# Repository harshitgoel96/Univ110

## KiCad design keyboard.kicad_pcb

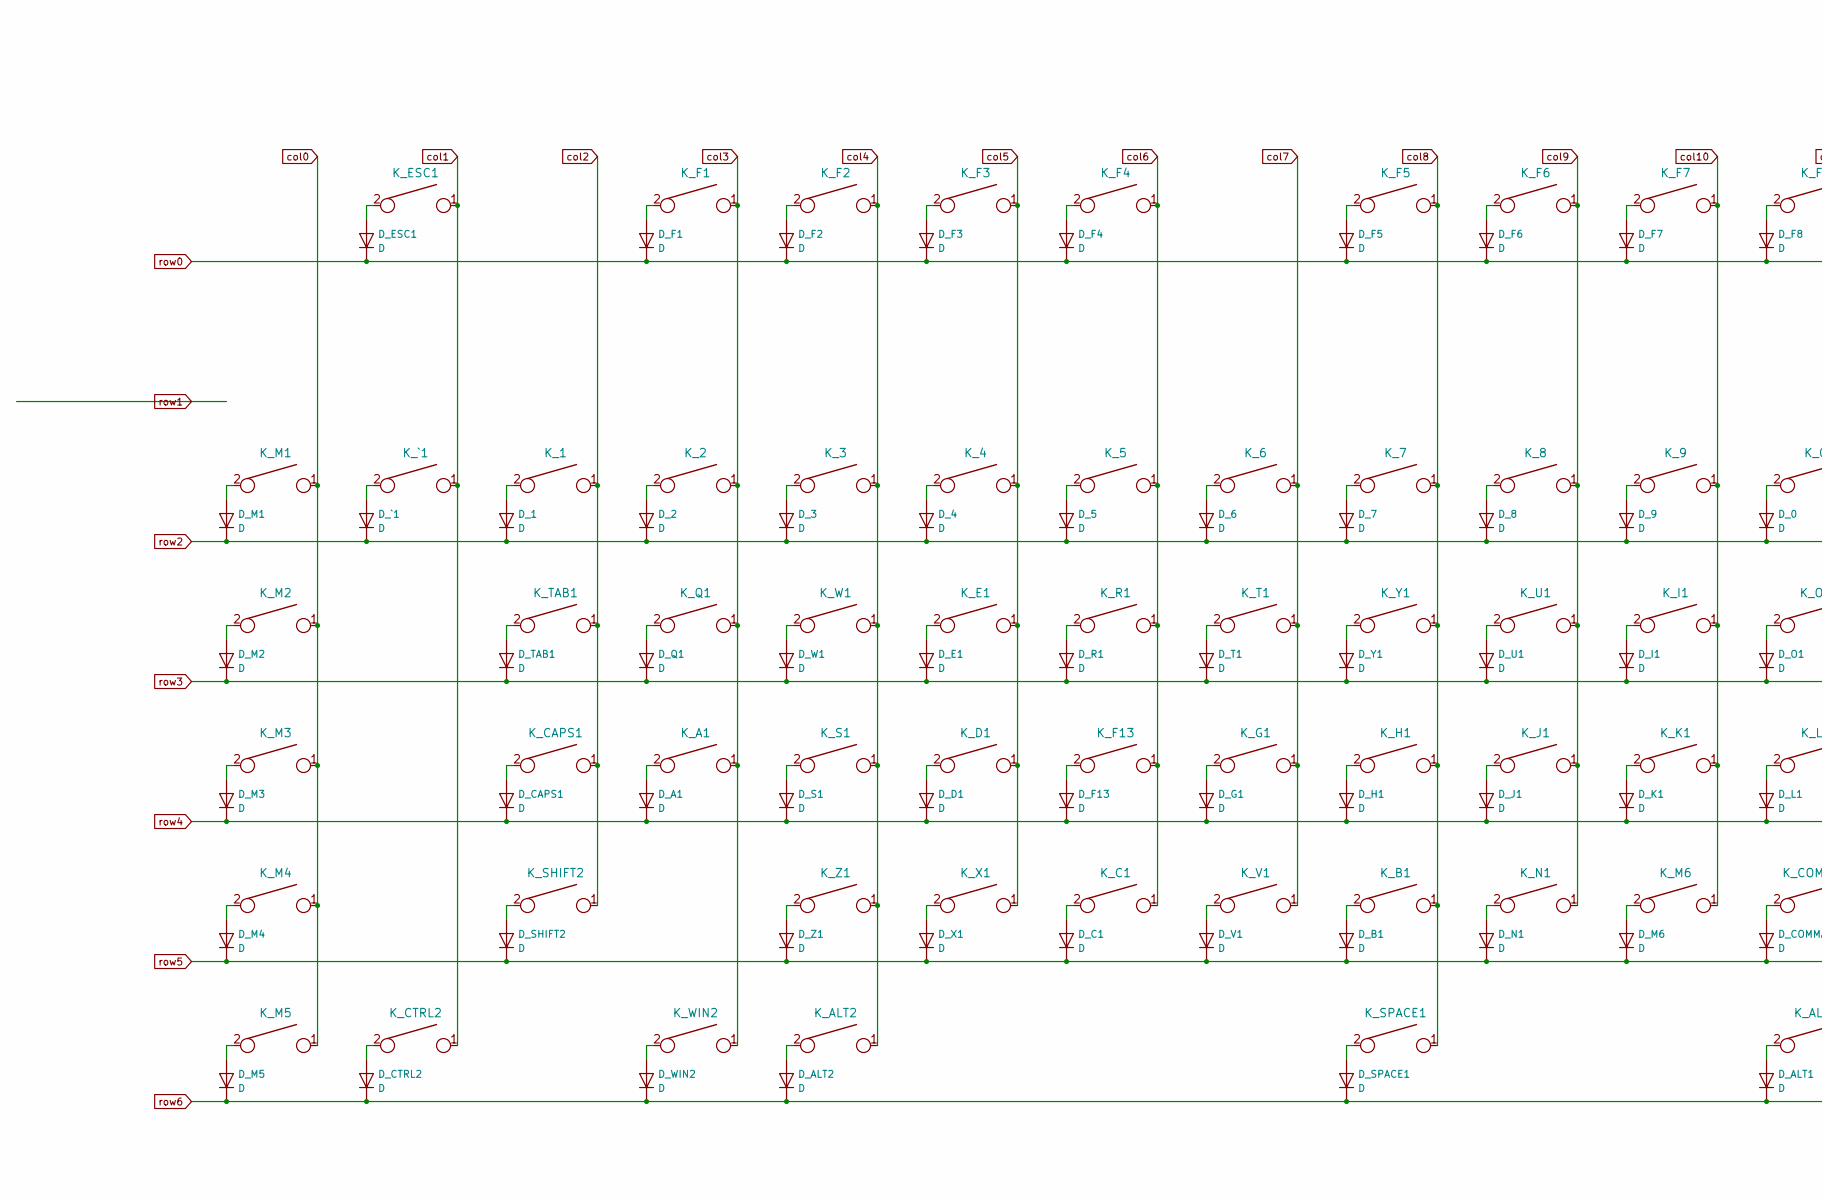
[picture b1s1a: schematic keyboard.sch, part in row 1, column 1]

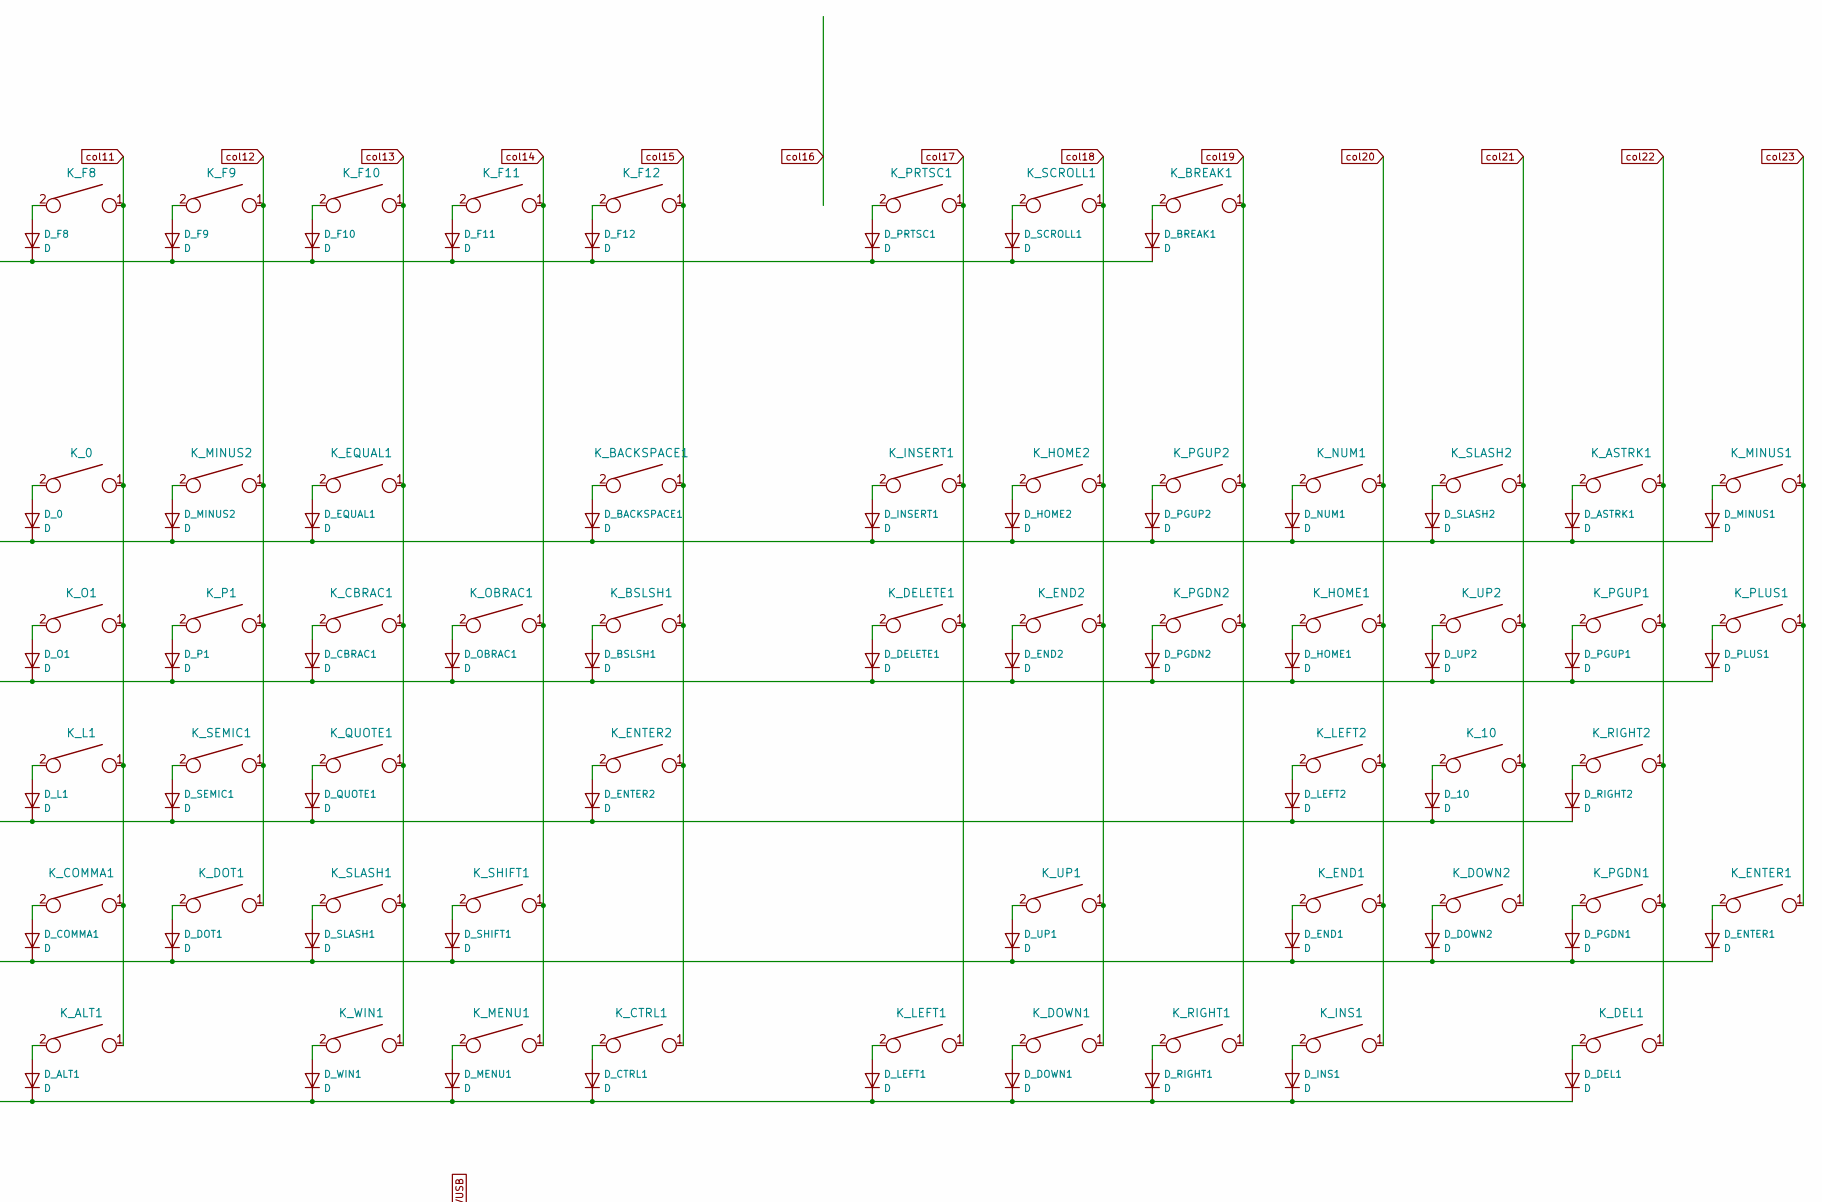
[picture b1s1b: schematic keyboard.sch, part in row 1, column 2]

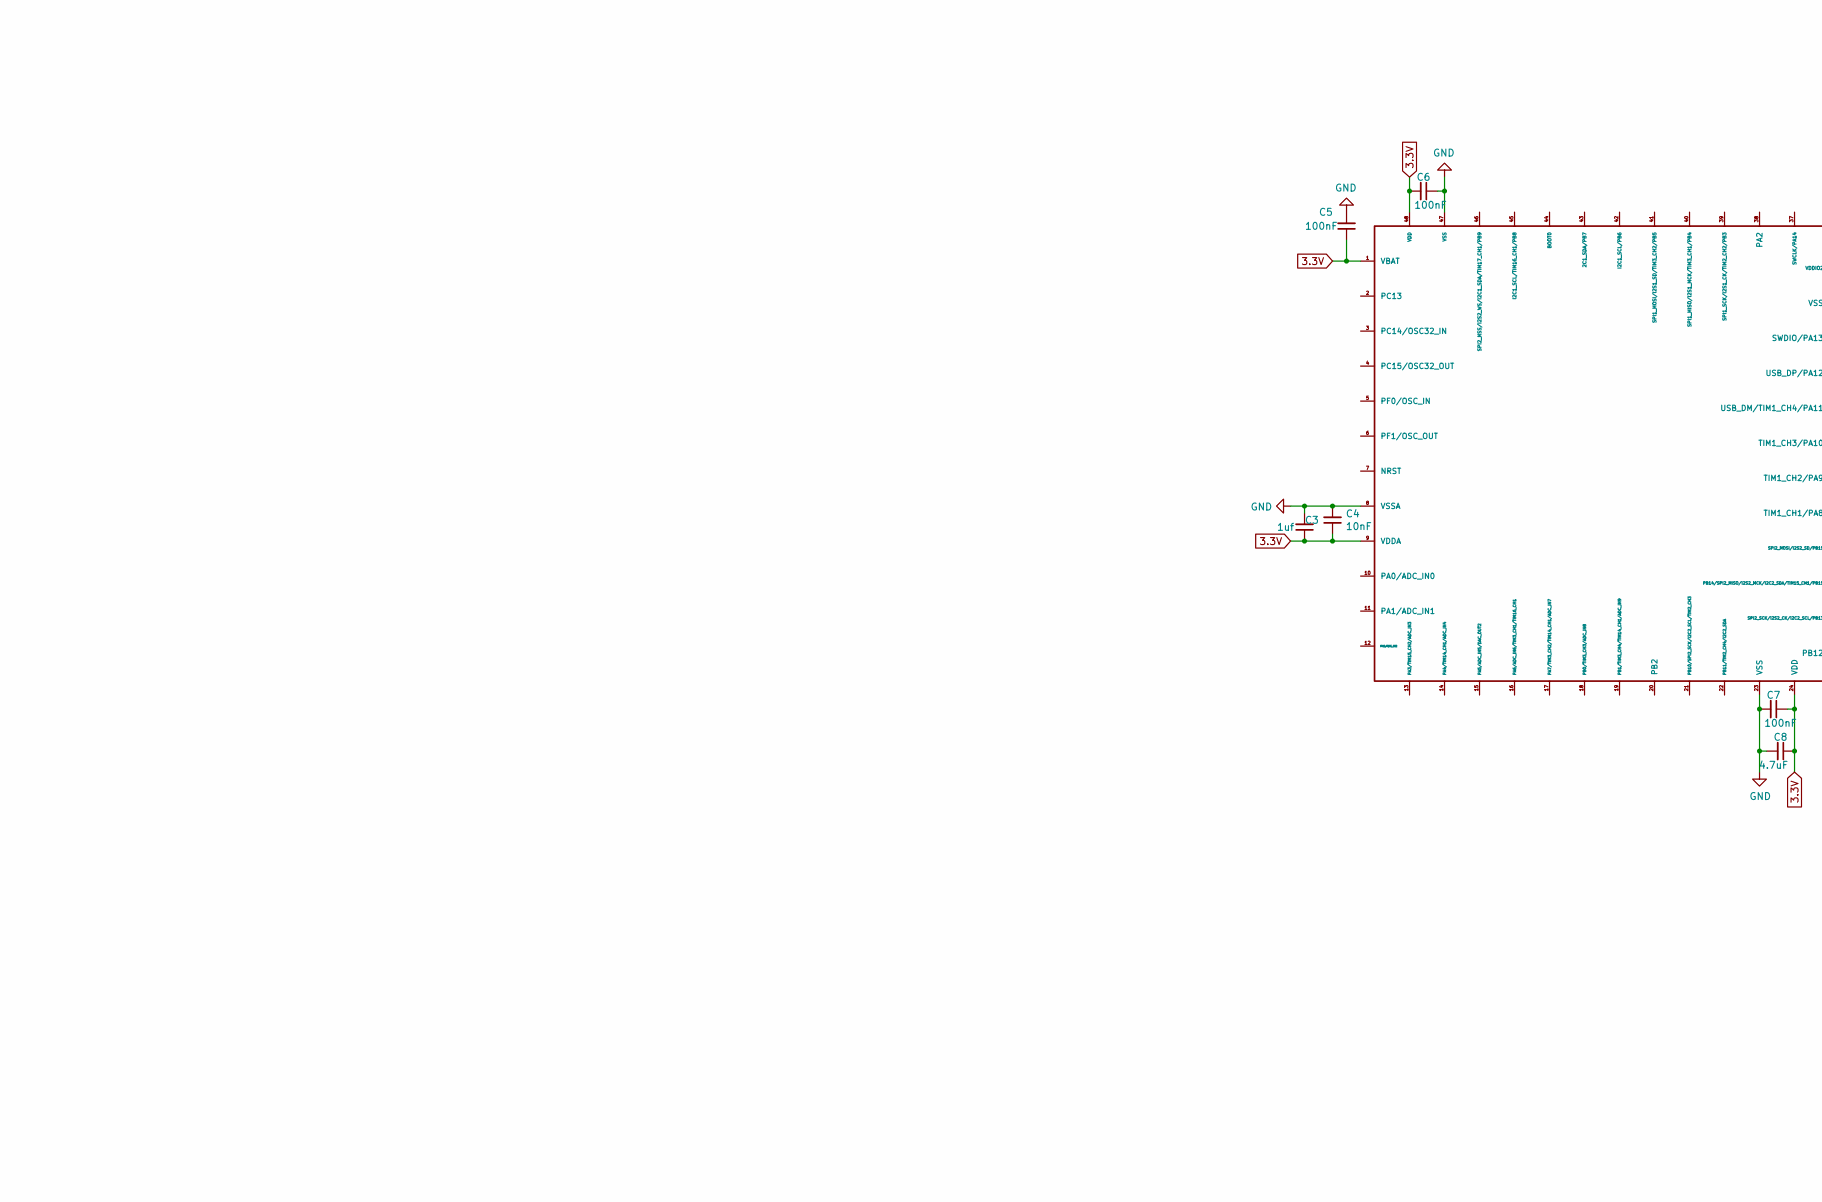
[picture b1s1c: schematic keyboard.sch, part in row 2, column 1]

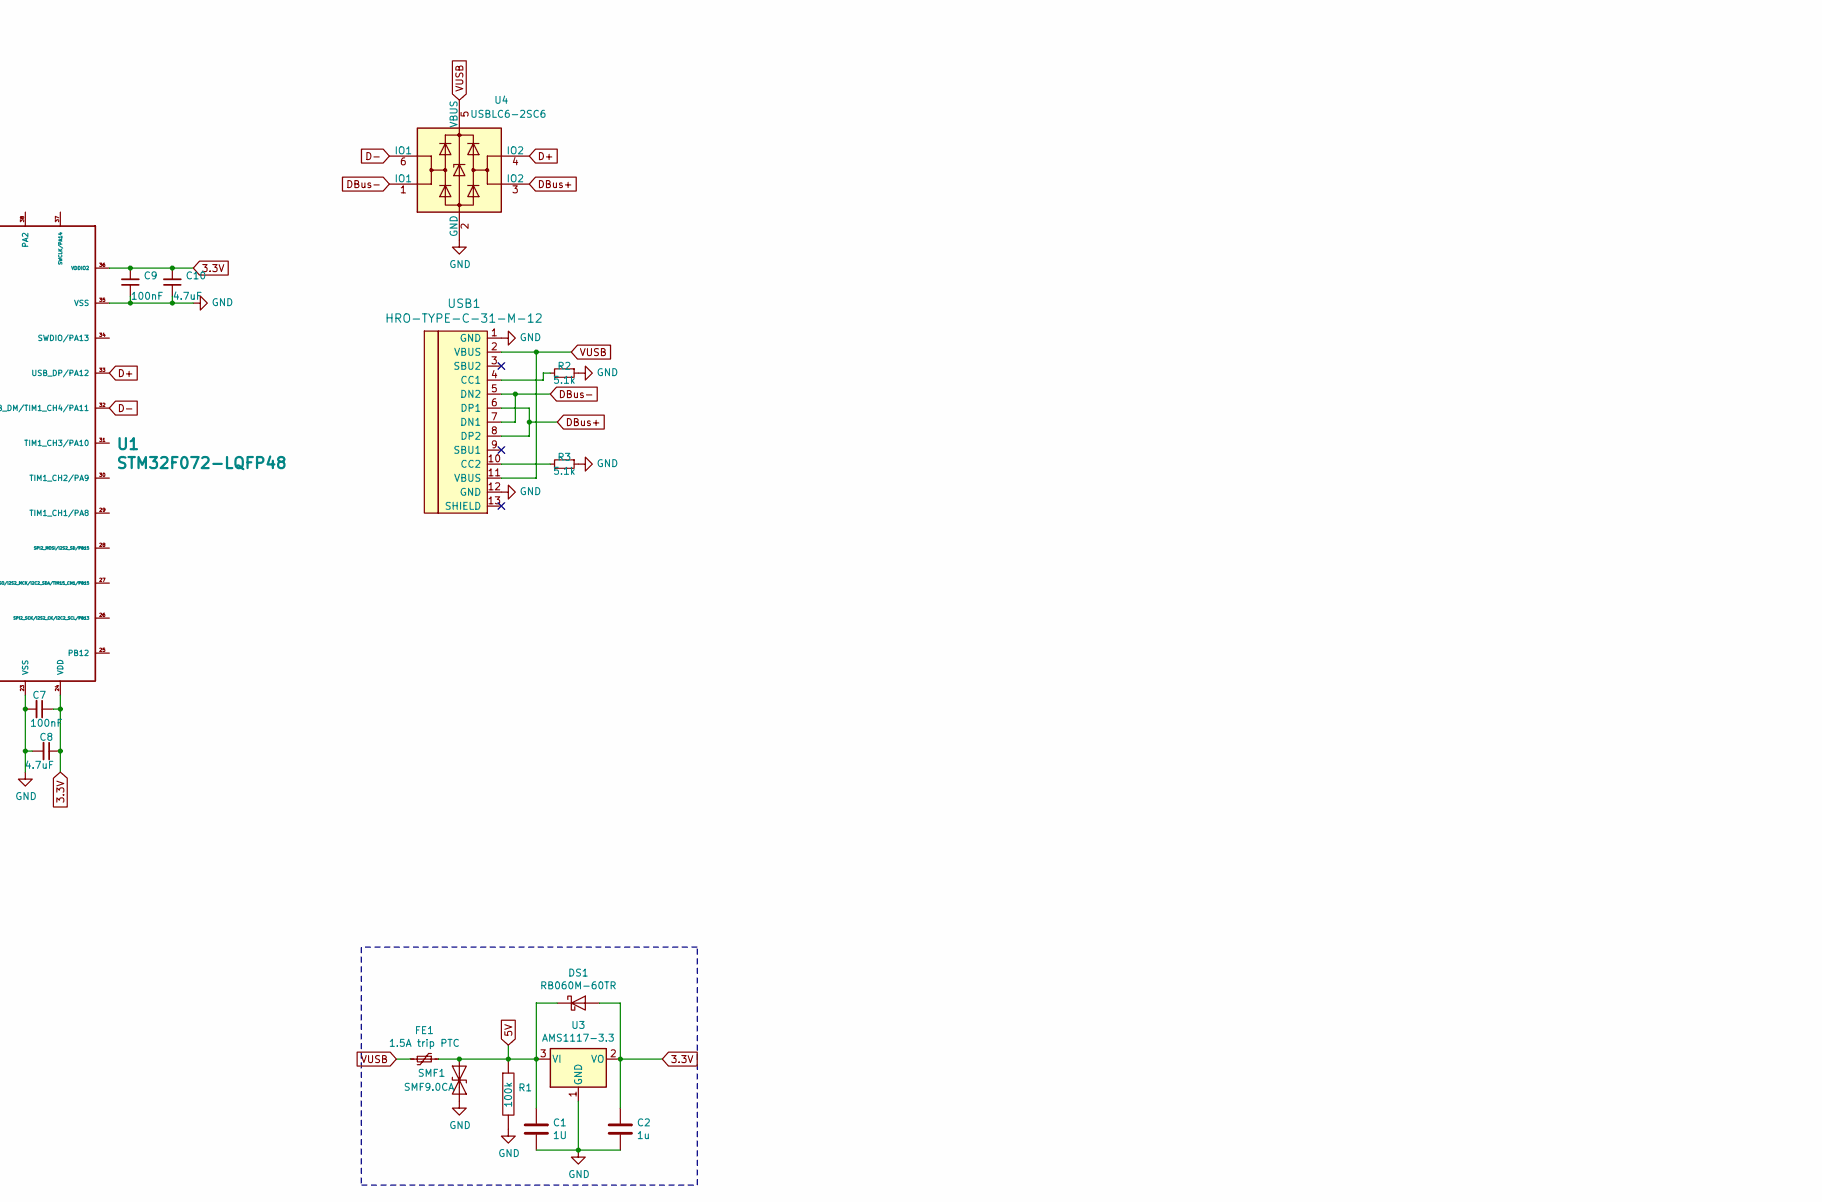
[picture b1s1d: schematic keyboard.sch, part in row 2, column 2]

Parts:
C1: 1U; C_0805_2012Metric_Pad1.15x1.40mm_HandSolder
C2: 1u; C_0805_2012Metric_Pad1.15x1.40mm_HandSolder
C3: 1uf; C_0805_2012Metric_Pad1.15x1.40mm_HandSolder
C4: 10nF; C_0805_2012Metric_Pad1.15x1.40mm_HandSolder
C5, C6, C7, C9: 100nF; C_0805_2012Metric_Pad1.15x1.40mm_HandSolder
C8, C10: 4.7uF; C_0805_2012Metric_Pad1.15x1.40mm_HandSolder
DS1: RB060M-60TR; D_SOD-123
D_0, D_1, D_2, D_3, D_4, D_5, D_6, D_7, D_8, D_9, D_10: D; D_SOD123_axial
D_A1: D; D_SOD123_axial
D_ALT1, D_ALT2: D; D_SOD123_axial
D_ASTRK1: D; D_SOD123_axial
D_B1: D; D_SOD123_axial
D_BACKSPACE1: D; D_SOD123_axial
D_BREAK1: D; D_SOD123_axial
D_BSLSH1: D; D_SOD123_axial
D_C1: D; D_SOD123_axial
D_CAPS1: D; D_SOD123_axial
D_CBRAC1: D; D_SOD123_axial
D_COMMA1: D; D_SOD123_axial
D_CTRL1, D_CTRL2: D; D_SOD123_axial
D_D1: D; D_SOD123_axial
D_DEL1: D; D_SOD123_axial
D_DELETE1: D; D_SOD123_axial
D_DOT1: D; D_SOD123_axial
D_DOWN1, D_DOWN2: D; D_SOD123_axial
D_E1: D; D_SOD123_axial
D_END1, D_END2: D; D_SOD123_axial
D_ENTER1, D_ENTER2: D; D_SOD123_axial
D_EQUAL1: D; D_SOD123_axial
D_ESC1: D; D_SOD123_axial
D_F1, D_F2, D_F3, D_F4, D_F5, D_F6, D_F7, D_F8, D_F9, D_F10, D_F11, D_F12, D_F13: D; D_SOD123_axial
D_G1: D; D_SOD123_axial
D_H1: D; D_SOD123_axial
D_HOME1, D_HOME2: D; D_SOD123_axial
D_I1: D; D_SOD123_axial
D_INS1: D; D_SOD123_axial
D_INSERT1: D; D_SOD123_axial
D_J1: D; D_SOD123_axial
D_K1: D; D_SOD123_axial
D_L1: D; D_SOD123_axial
D_LEFT1, D_LEFT2: D; D_SOD123_axial
D_M1, D_M2, D_M3, D_M4, D_M5, D_M6: D; D_SOD123_axial
D_MENU1: D; D_SOD123_axial
D_MINUS1, D_MINUS2: D; D_SOD123_axial
D_N1: D; D_SOD123_axial
D_NUM1: D; D_SOD123_axial
D_O1: D; D_SOD123_axial
D_OBRAC1: D; D_SOD123_axial
D_P1: D; D_SOD123_axial
D_PGDN1, D_PGDN2: D; D_SOD123_axial
D_PGUP1, D_PGUP2: D; D_SOD123_axial
D_PLUS1: D; D_SOD123_axial
D_PRTSC1: D; D_SOD123_axial
D_Q1: D; D_SOD123_axial
D_QUOTE1: D; D_SOD123_axial
D_R1: D; D_SOD123_axial
D_RIGHT1, D_RIGHT2: D; D_SOD123_axial
D_S1: D; D_SOD123_axial
D_SCROLL1: D; D_SOD123_axial
D_SEMIC1: D; D_SOD123_axial
D_SHIFT1, D_SHIFT2: D; D_SOD123_axial
D_SLASH1, D_SLASH2: D; D_SOD123_axial
D_SPACE1: D; D_SOD123_axial
D_T1: D; D_SOD123_axial
D_TAB1: D; D_SOD123_axial
D_U1: D; D_SOD123_axial
D_UP1, D_UP2: D; D_SOD123_axial
D_V1: D; D_SOD123_axial
D_W1: D; D_SOD123_axial
D_WIN1, D_WIN2: D; D_SOD123_axial
D_X1: D; D_SOD123_axial
D_Y1: D; D_SOD123_axial
D_Z1: D; D_SOD123_axial
D_`1: D; D_SOD123_axial
FE1: 1.5A trip PTC; Fuse_1812_4532
K_0, K_1, K_2, K_3, K_4, K_5, K_6, K_7, K_8, K_9, K_10: KEYSW; MX-ALPs-PG1350-FLIP
K_A1: KEYSW; MX-ALPs-PG1350-FLIP
K_ALT1, K_ALT2: KEYSW; MX-ALPs-PG1350-FLIP
K_ASTRK1: KEYSW; MX-ALPs-PG1350-FLIP
K_B1: KEYSW; MX-ALPs-PG1350-FLIP
K_BACKSPACE1: KEYSW; MX-ALPs-PG1350-FLIP-2U-FLIP
K_BREAK1: KEYSW; MX-ALPs-PG1350-FLIP
K_BSLSH1: KEYSW; MX-ALPs-PG1350-FLIP
K_C1: KEYSW; MX-ALPs-PG1350-FLIP
K_CAPS1: KEYSW; MX-ALPs-PG1350-FLIP
K_CBRAC1: KEYSW; MX-ALPs-PG1350-FLIP
K_COMMA1: KEYSW; MX-ALPs-PG1350-FLIP
K_CTRL1, K_CTRL2: KEYSW; MX-ALPs-PG1350-FLIP
K_D1: KEYSW; MX-ALPs-PG1350-FLIP
K_DEL1: KEYSW; MX-ALPs-PG1350-FLIP
K_DELETE1: KEYSW; MX-ALPs-PG1350-FLIP
K_DOT1: KEYSW; MX-ALPs-PG1350-FLIP
K_DOWN1, K_DOWN2: KEYSW; MX-ALPs-PG1350-FLIP
K_E1: KEYSW; MX-ALPs-PG1350-FLIP
K_END1, K_END2: KEYSW; MX-ALPs-PG1350-FLIP
K_ENTER1: KEYSW; MX-ALPs-PG1350-FLIP-2U
K_ENTER2: KEYSW; MX-ALPs-PG1350-FLIP-2U-FLIP
K_EQUAL1: KEYSW; MX-ALPs-PG1350-FLIP
K_ESC1: KEYSW; MX-ALPs-PG1350-FLIP
K_F1, K_F2, K_F3, K_F4, K_F5, K_F6, K_F7, K_F8, K_F9, K_F10, K_F11, K_F12, K_F13: KEYSW; MX-ALPs-PG1350-FLIP
K_G1: KEYSW; MX-ALPs-PG1350-FLIP
K_H1: KEYSW; MX-ALPs-PG1350-FLIP
K_HOME1, K_HOME2: KEYSW; MX-ALPs-PG1350-FLIP
K_I1: KEYSW; MX-ALPs-PG1350-FLIP
K_INS1: KEYSW; MX-ALPs-PG1350-FLIP-2U
K_INSERT1: KEYSW; MX-ALPs-PG1350-FLIP
K_J1: KEYSW; MX-ALPs-PG1350-FLIP
K_K1: KEYSW; MX-ALPs-PG1350-FLIP
K_L1: KEYSW; MX-ALPs-PG1350-FLIP
K_LEFT1, K_LEFT2: KEYSW; MX-ALPs-PG1350-FLIP
K_M1, K_M2, K_M3, K_M4, K_M5, K_M6: KEYSW; MX-ALPs-PG1350-FLIP
K_MENU1: KEYSW; MX-ALPs-PG1350-FLIP
K_MINUS1, K_MINUS2: KEYSW; MX-ALPs-PG1350-FLIP
K_N1: KEYSW; MX-ALPs-PG1350-FLIP
K_NUM1: KEYSW; MX-ALPs-PG1350-FLIP
K_O1: KEYSW; MX-ALPs-PG1350-FLIP
K_OBRAC1: KEYSW; MX-ALPs-PG1350-FLIP
K_P1: KEYSW; MX-ALPs-PG1350-FLIP
K_PGDN1, K_PGDN2: KEYSW; MX-ALPs-PG1350-FLIP
K_PGUP1, K_PGUP2: KEYSW; MX-ALPs-PG1350-FLIP
K_PLUS1: KEYSW; MX-ALPs-PG1350-FLIP-2U
K_PRTSC1: KEYSW; MX-ALPs-PG1350-FLIP
K_Q1: KEYSW; MX-ALPs-PG1350-FLIP
K_QUOTE1: KEYSW; MX-ALPs-PG1350-FLIP
K_R1: KEYSW; MX-ALPs-PG1350-FLIP
K_RIGHT1, K_RIGHT2: KEYSW; MX-ALPs-PG1350-FLIP
K_S1: KEYSW; MX-ALPs-PG1350-FLIP
K_SCROLL1: KEYSW; MX-ALPs-PG1350-FLIP
K_SEMIC1: KEYSW; MX-ALPs-PG1350-FLIP
K_SHIFT1, K_SHIFT2: KEYSW; MX-ALPs-PG1350-FLIP-2U-FLIP
K_SLASH1, K_SLASH2: KEYSW; MX-ALPs-PG1350-FLIP
K_SPACE1: KEYSW; MX625_base
K_T1: KEYSW; MX-ALPs-PG1350-FLIP
K_TAB1: KEYSW; MX-ALPs-PG1350-FLIP
K_U1: KEYSW; MX-ALPs-PG1350-FLIP
K_UP1, K_UP2: KEYSW; MX-ALPs-PG1350-FLIP
K_V1: KEYSW; MX-ALPs-PG1350-FLIP
K_W1: KEYSW; MX-ALPs-PG1350-FLIP
K_WIN1, K_WIN2: KEYSW; MX-ALPs-PG1350-FLIP
K_X1: KEYSW; MX-ALPs-PG1350-FLIP
K_Y1: KEYSW; MX-ALPs-PG1350-FLIP
K_Z1: KEYSW; MX-ALPs-PG1350-FLIP
K_`1: KEYSW; MX-ALPs-PG1350-FLIP
R1: 100k; R_0805
R2, R3: 5.1k; R_0805
SMF1: SMF9.0CA; D_SOD-123
U1: STM32F072-LQFP48; LQFP-48_7x7mm_P0.5mm
U3: AMS1117-3.3; SOT-223-3_TabPin2
U4: USBLC6-2SC6; SOT-23-6
USB1: HRO-TYPE-C-31-M-12; HRO-TYPE-C-31-M-12-HandSoldering

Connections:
3.3V: C2.1, C3.1, C4.1, C5.1, C6.2, C7.1, C8.1, C9.2, C10.2, DS1.2 (A), U1.1 (VBAT), U1.9 (VDDA), U1.24 (VDD), U1.36 (VDDIO2), U1.48 (VDD), U3.2 (VO)
5V: C1.1, DS1.1 (K), FE1.1, R1.1, SMF1.1 (A1), U3.3 (VI)
D+: U1.33 (USB_DP/PA12), U4.4 (IO2)
D-: U1.32 (USB_DM/TIM1_CH4/PA11), U4.6 (IO1)
DBus+: U4.3 (IO2), USB1.6 (DP1), USB1.8 (DP2)
DBus-: U4.1 (IO1), USB1.5 (DN2), USB1.7 (DN1)
GND: C1.2, C2.2, C3.2, C4.2, C5.2, C6.1, C7.2, C8.2, C9.1, C10.1, R1.2, R2.1, R3.1, SMF1.2 (A2), U1.8 (VSSA), U1.23 (VSS), U1.35 (VSS), U1.47 (VSS), U3.1 (GND), U4.2 (GND), USB1.1 (GND), USB1.12 (GND)
unnamed: D_0.2 (A), K_0.2
unnamed: D_1.2 (A), K_1.2
unnamed: D_2.2 (A), K_2.2
unnamed: D_3.2 (A), K_3.2
unnamed: D_4.2 (A), K_4.2
unnamed: D_5.2 (A), K_5.2
unnamed: D_6.2 (A), K_6.2
unnamed: D_7.2 (A), K_7.2
unnamed: D_8.2 (A), K_8.2
unnamed: D_9.2 (A), K_9.2
unnamed: D_10.2 (A), K_10.2
unnamed: D_A1.2 (A), K_A1.2
unnamed: D_ALT1.2 (A), K_ALT1.2
unnamed: D_ALT2.2 (A), K_ALT2.2
unnamed: D_ASTRK1.2 (A), K_ASTRK1.2
unnamed: D_B1.2 (A), K_B1.2
unnamed: D_BACKSPACE1.2 (A), K_BACKSPACE1.2
unnamed: D_BREAK1.2 (A), K_BREAK1.2
unnamed: D_BSLSH1.2 (A), K_BSLSH1.2
unnamed: D_C1.2 (A), K_C1.2
unnamed: D_CAPS1.2 (A), K_CAPS1.2
unnamed: D_CBRAC1.2 (A), K_CBRAC1.2
unnamed: D_COMMA1.2 (A), K_COMMA1.2
unnamed: D_CTRL1.2 (A), K_CTRL1.2
unnamed: D_CTRL2.2 (A), K_CTRL2.2
unnamed: D_D1.2 (A), K_D1.2
unnamed: D_DEL1.2 (A), K_DEL1.2
unnamed: D_DELETE1.2 (A), K_DELETE1.2
unnamed: D_DOT1.2 (A), K_DOT1.2
unnamed: D_DOWN1.2 (A), K_DOWN1.2
unnamed: D_DOWN2.2 (A), K_DOWN2.2
unnamed: D_E1.2 (A), K_E1.2
unnamed: D_END1.2 (A), K_END1.2
unnamed: D_END2.2 (A), K_END2.2
unnamed: D_ENTER1.2 (A), K_ENTER1.2
unnamed: D_ENTER2.2 (A), K_ENTER2.2
unnamed: D_EQUAL1.2 (A), K_EQUAL1.2
unnamed: D_ESC1.2 (A), K_ESC1.2
unnamed: D_F1.2 (A), K_F1.2
unnamed: D_F2.2 (A), K_F2.2
unnamed: D_F3.2 (A), K_F3.2
unnamed: D_F4.2 (A), K_F4.2
unnamed: D_F5.2 (A), K_F5.2
unnamed: D_F6.2 (A), K_F6.2
unnamed: D_F7.2 (A), K_F7.2
unnamed: D_F8.2 (A), K_F8.2
unnamed: D_F9.2 (A), K_F9.2
unnamed: D_F10.2 (A), K_F10.2
unnamed: D_F11.2 (A), K_F11.2
unnamed: D_F12.2 (A), K_F12.2
unnamed: D_F13.2 (A), K_F13.2
unnamed: D_G1.2 (A), K_G1.2
unnamed: D_H1.2 (A), K_H1.2
unnamed: D_HOME1.2 (A), K_HOME1.2
unnamed: D_HOME2.2 (A), K_HOME2.2
unnamed: D_I1.2 (A), K_I1.2
unnamed: D_INS1.2 (A), K_INS1.2
unnamed: D_INSERT1.2 (A), K_INSERT1.2
unnamed: D_J1.2 (A), K_J1.2
unnamed: D_K1.2 (A), K_K1.2
unnamed: D_L1.2 (A), K_L1.2
unnamed: D_LEFT1.2 (A), K_LEFT1.2
unnamed: D_LEFT2.2 (A), K_LEFT2.2
unnamed: D_M1.2 (A), K_M1.2
unnamed: D_M2.2 (A), K_M2.2
unnamed: D_M3.2 (A), K_M3.2
unnamed: D_M4.2 (A), K_M4.2
unnamed: D_M5.2 (A), K_M5.2
unnamed: D_M6.2 (A), K_M6.2
unnamed: D_MENU1.2 (A), K_MENU1.2
unnamed: D_MINUS1.2 (A), K_MINUS1.2
unnamed: D_MINUS2.2 (A), K_MINUS2.2
unnamed: D_N1.2 (A), K_N1.2
unnamed: D_NUM1.2 (A), K_NUM1.2
unnamed: D_O1.2 (A), K_O1.2
unnamed: D_OBRAC1.2 (A), K_OBRAC1.2
unnamed: D_P1.2 (A), K_P1.2
unnamed: D_PGDN1.2 (A), K_PGDN1.2
unnamed: D_PGDN2.2 (A), K_PGDN2.2
unnamed: D_PGUP1.2 (A), K_PGUP1.2
unnamed: D_PGUP2.2 (A), K_PGUP2.2
unnamed: D_PLUS1.2 (A), K_PLUS1.2
unnamed: D_PRTSC1.2 (A), K_PRTSC1.2
unnamed: D_Q1.2 (A), K_Q1.2
unnamed: D_QUOTE1.2 (A), K_QUOTE1.2
unnamed: D_R1.2 (A), K_R1.2
unnamed: D_RIGHT1.2 (A), K_RIGHT1.2
unnamed: D_RIGHT2.2 (A), K_RIGHT2.2
unnamed: D_S1.2 (A), K_S1.2
unnamed: D_SCROLL1.2 (A), K_SCROLL1.2
unnamed: D_SEMIC1.2 (A), K_SEMIC1.2
unnamed: D_SHIFT1.2 (A), K_SHIFT1.2
unnamed: D_SHIFT2.2 (A), K_SHIFT2.2
unnamed: D_SLASH1.2 (A), K_SLASH1.2
unnamed: D_SLASH2.2 (A), K_SLASH2.2
unnamed: D_SPACE1.2 (A), K_SPACE1.2
unnamed: D_T1.2 (A), K_T1.2
unnamed: D_TAB1.2 (A), K_TAB1.2
unnamed: D_U1.2 (A), K_U1.2
unnamed: D_UP1.2 (A), K_UP1.2
unnamed: D_UP2.2 (A), K_UP2.2
unnamed: D_V1.2 (A), K_V1.2
unnamed: D_W1.2 (A), K_W1.2
unnamed: D_WIN1.2 (A), K_WIN1.2
unnamed: D_WIN2.2 (A), K_WIN2.2
unnamed: D_X1.2 (A), K_X1.2
unnamed: D_Y1.2 (A), K_Y1.2
unnamed: D_Z1.2 (A), K_Z1.2
unnamed: D_`1.2 (A), K_`1.2
unnamed: R2.2, USB1.4 (CC1)
unnamed: R3.2, USB1.10 (CC2)
VUSB: FE1.2, U4.5 (VBUS), USB1.2 (VBUS), USB1.11 (VBUS)
col0: K_M1.1, K_M2.1, K_M3.1, K_M4.1, K_M5.1
col1: K_CTRL2.1, K_ESC1.1, K_`1.1
col2: K_1.1, K_CAPS1.1, K_SHIFT2.1, K_TAB1.1
col3: K_2.1, K_A1.1, K_F1.1, K_Q1.1, K_WIN2.1
col4: K_3.1, K_ALT2.1, K_F2.1, K_S1.1, K_W1.1, K_Z1.1
col5: K_4.1, K_D1.1, K_E1.1, K_F3.1, K_X1.1
col6: K_5.1, K_C1.1, K_F4.1, K_F13.1, K_R1.1
col7: K_6.1, K_G1.1, K_T1.1, K_V1.1
col8: K_7.1, K_B1.1, K_F5.1, K_H1.1, K_SPACE1.1, K_Y1.1
col9: K_8.1, K_F6.1, K_J1.1, K_N1.1, K_U1.1
col10: K_9.1, K_F7.1, K_I1.1, K_K1.1, K_M6.1
col11: K_0.1, K_ALT1.1, K_COMMA1.1, K_F8.1, K_L1.1, K_O1.1
col12: K_DOT1.1, K_F9.1, K_MINUS2.1, K_P1.1, K_SEMIC1.1
col13: K_CBRAC1.1, K_EQUAL1.1, K_F10.1, K_QUOTE1.1, K_SLASH1.1, K_WIN1.1
col14: K_F11.1, K_MENU1.1, K_OBRAC1.1, K_SHIFT1.1
col15: K_BACKSPACE1.1, K_BSLSH1.1, K_CTRL1.1, K_ENTER2.1, K_F12.1
col17: K_DELETE1.1, K_INSERT1.1, K_LEFT1.1, K_PRTSC1.1
col18: K_DOWN1.1, K_END2.1, K_HOME2.1, K_SCROLL1.1, K_UP1.1
col19: K_BREAK1.1, K_PGDN2.1, K_PGUP2.1, K_RIGHT1.1
col20: K_END1.1, K_HOME1.1, K_INS1.1, K_LEFT2.1, K_NUM1.1
col21: K_10.1, K_DOWN2.1, K_SLASH2.1, K_UP2.1
col22: K_ASTRK1.1, K_DEL1.1, K_PGDN1.1, K_PGUP1.1, K_RIGHT2.1
col23: K_ENTER1.1, K_MINUS1.1, K_PLUS1.1
row0: D_BREAK1.1 (K), D_ESC1.1 (K), D_F1.1 (K), D_F2.1 (K), D_F3.1 (K), D_F4.1 (K), D_F5.1 (K), D_F6.1 (K), D_F7.1 (K), D_F8.1 (K), D_F9.1 (K), D_F10.1 (K), D_F11.1 (K), D_F12.1 (K), D_PRTSC1.1 (K), D_SCROLL1.1 (K)
row2: D_0.1 (K), D_1.1 (K), D_2.1 (K), D_3.1 (K), D_4.1 (K), D_5.1 (K), D_6.1 (K), D_7.1 (K), D_8.1 (K), D_9.1 (K), D_ASTRK1.1 (K), D_BACKSPACE1.1 (K), D_EQUAL1.1 (K), D_HOME2.1 (K), D_INSERT1.1 (K), D_M1.1 (K), D_MINUS1.1 (K), D_MINUS2.1 (K), D_NUM1.1 (K), D_PGUP2.1 (K), D_SLASH2.1 (K), D_`1.1 (K)
row3: D_BSLSH1.1 (K), D_CBRAC1.1 (K), D_DELETE1.1 (K), D_E1.1 (K), D_END2.1 (K), D_HOME1.1 (K), D_I1.1 (K), D_M2.1 (K), D_O1.1 (K), D_OBRAC1.1 (K), D_P1.1 (K), D_PGDN2.1 (K), D_PGUP1.1 (K), D_PLUS1.1 (K), D_Q1.1 (K), D_R1.1 (K), D_T1.1 (K), D_TAB1.1 (K), D_U1.1 (K), D_UP2.1 (K), D_W1.1 (K), D_Y1.1 (K)
row4: D_10.1 (K), D_A1.1 (K), D_CAPS1.1 (K), D_D1.1 (K), D_ENTER2.1 (K), D_F13.1 (K), D_G1.1 (K), D_H1.1 (K), D_J1.1 (K), D_K1.1 (K), D_L1.1 (K), D_LEFT2.1 (K), D_M3.1 (K), D_QUOTE1.1 (K), D_RIGHT2.1 (K), D_S1.1 (K), D_SEMIC1.1 (K)
row5: D_B1.1 (K), D_C1.1 (K), D_COMMA1.1 (K), D_DOT1.1 (K), D_DOWN2.1 (K), D_END1.1 (K), D_ENTER1.1 (K), D_M4.1 (K), D_M6.1 (K), D_N1.1 (K), D_PGDN1.1 (K), D_SHIFT1.1 (K), D_SHIFT2.1 (K), D_SLASH1.1 (K), D_UP1.1 (K), D_V1.1 (K), D_X1.1 (K), D_Z1.1 (K)
row6: D_ALT1.1 (K), D_ALT2.1 (K), D_CTRL1.1 (K), D_CTRL2.1 (K), D_DEL1.1 (K), D_DOWN1.1 (K), D_INS1.1 (K), D_LEFT1.1 (K), D_M5.1 (K), D_MENU1.1 (K), D_RIGHT1.1 (K), D_SPACE1.1 (K), D_WIN1.1 (K), D_WIN2.1 (K)

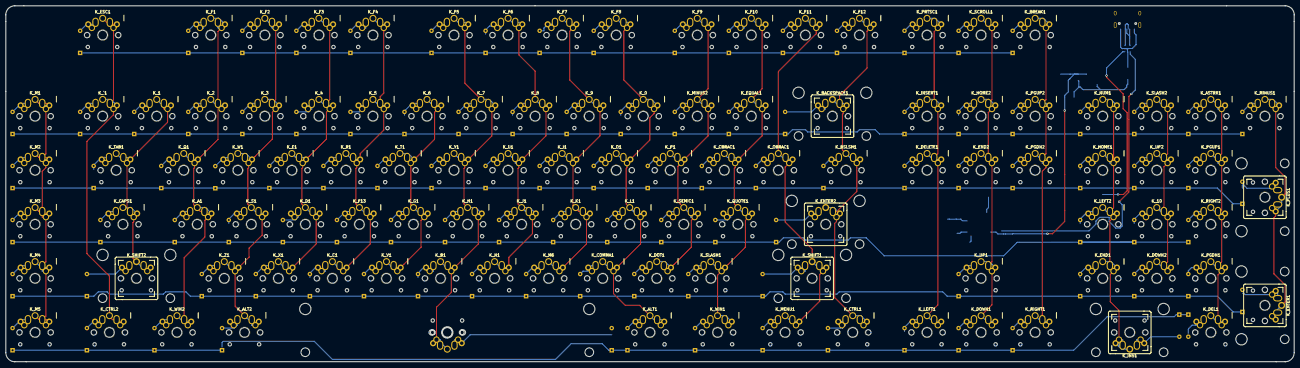
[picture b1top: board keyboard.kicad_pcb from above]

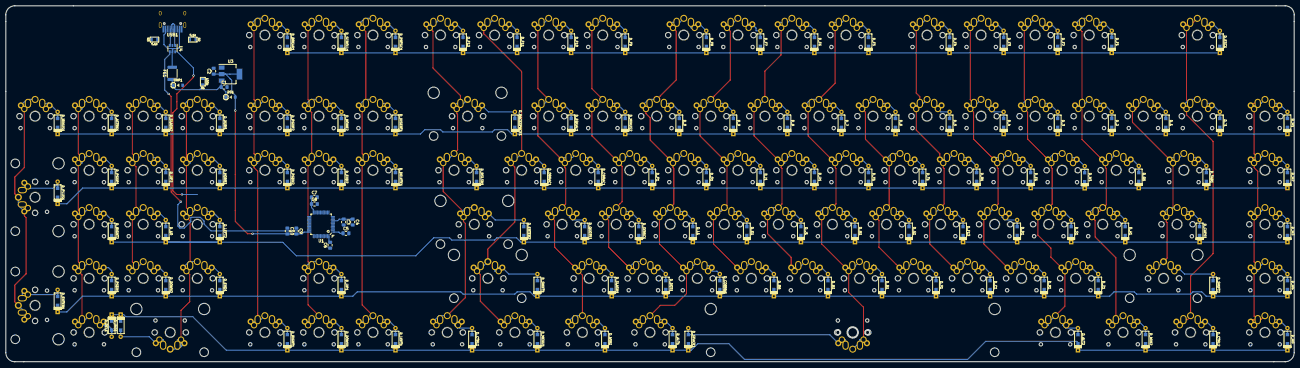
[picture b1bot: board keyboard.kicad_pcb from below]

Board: 2 copper layers, 454.0 x 125.4 mm, 238 parts (129 on the bottom side), 148 nets.

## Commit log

2020-05-04 inital git push. almost complete keyboard
2020-05-05 power supply completion
